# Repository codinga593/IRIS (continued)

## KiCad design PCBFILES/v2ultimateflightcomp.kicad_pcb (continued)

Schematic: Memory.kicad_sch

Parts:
C1: 10uF; C_0402_1005Metric
IC1: W25Q128JVFIQ; SOIC127P1032X264-16N; Mouser Part Number 454-W25Q128JVFIQ
R11: 10k; R_0402_1005Metric

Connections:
+3V3: C1.2, IC1.1 (IO3), IC1.2 (VCC), IC1.9 (IO2), R11.1; also elsewhere on the board
CS_FLASH: IC1.7 (~CS), R11.2; also elsewhere on the board
GND: C1.1, IC1.10 (GND); also elsewhere on the board
MISO_FLASH: IC1.8 (DO_(IO1)); also elsewhere on the board
MOSI_FLASH: IC1.15 (DI_(IO0)); also elsewhere on the board
SCK_FLASH: IC1.16 (CLK); also elsewhere on the board

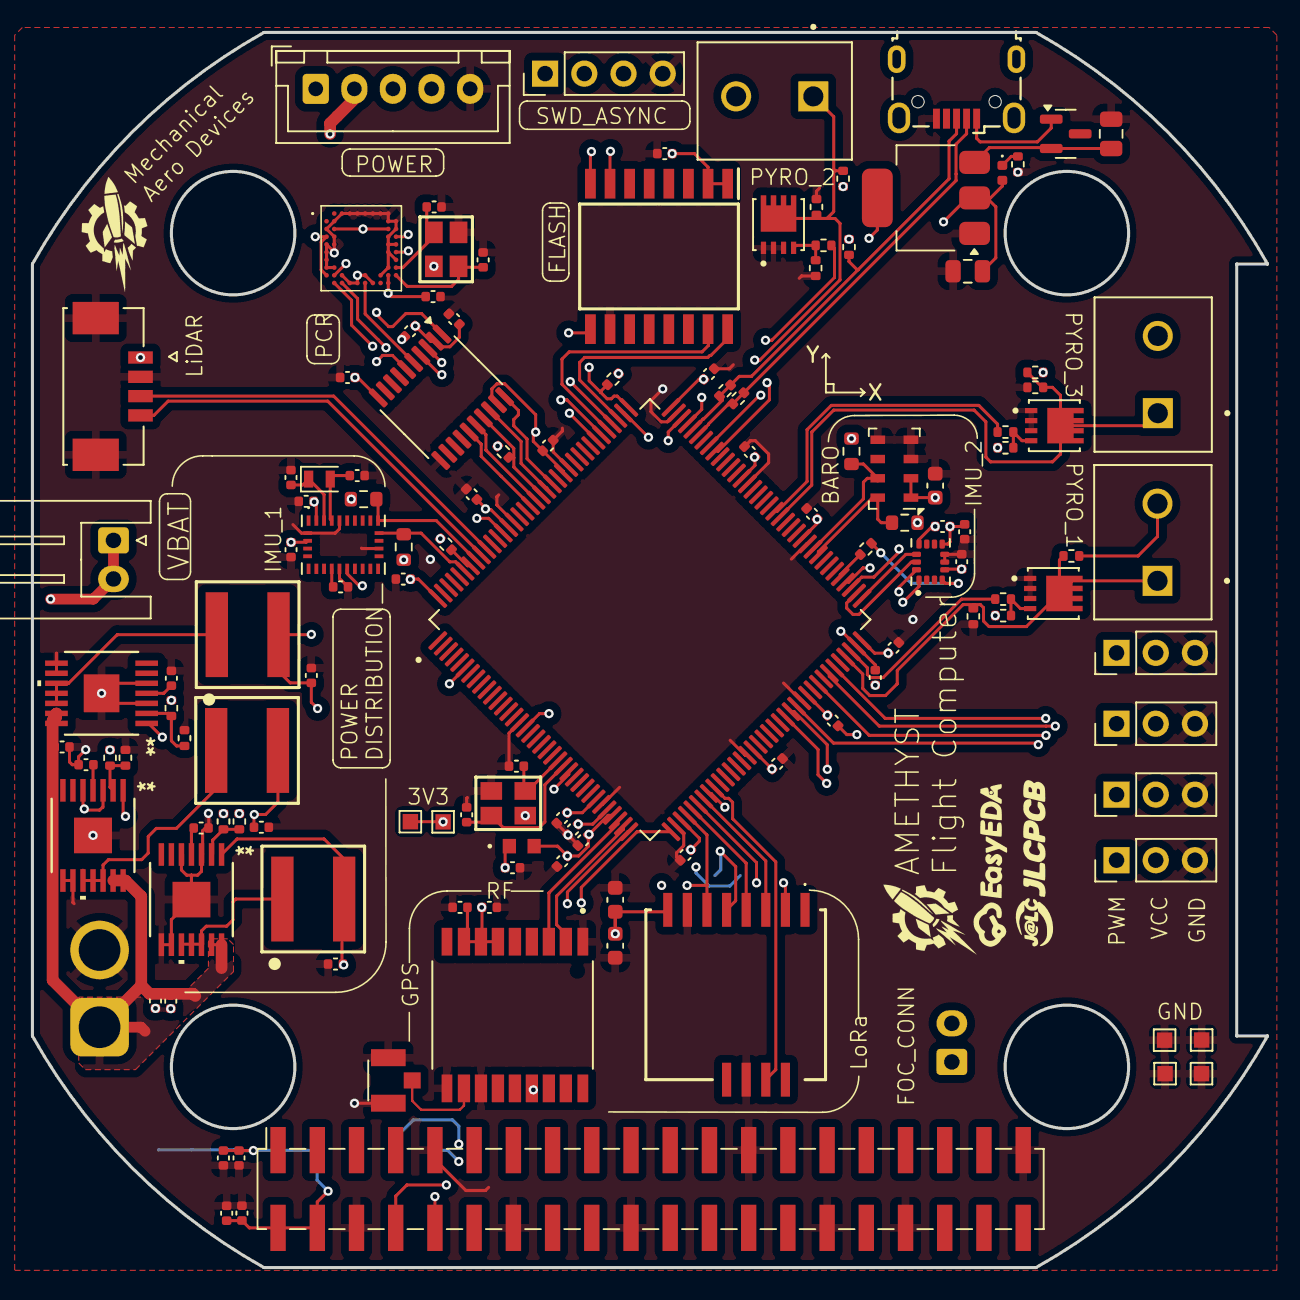
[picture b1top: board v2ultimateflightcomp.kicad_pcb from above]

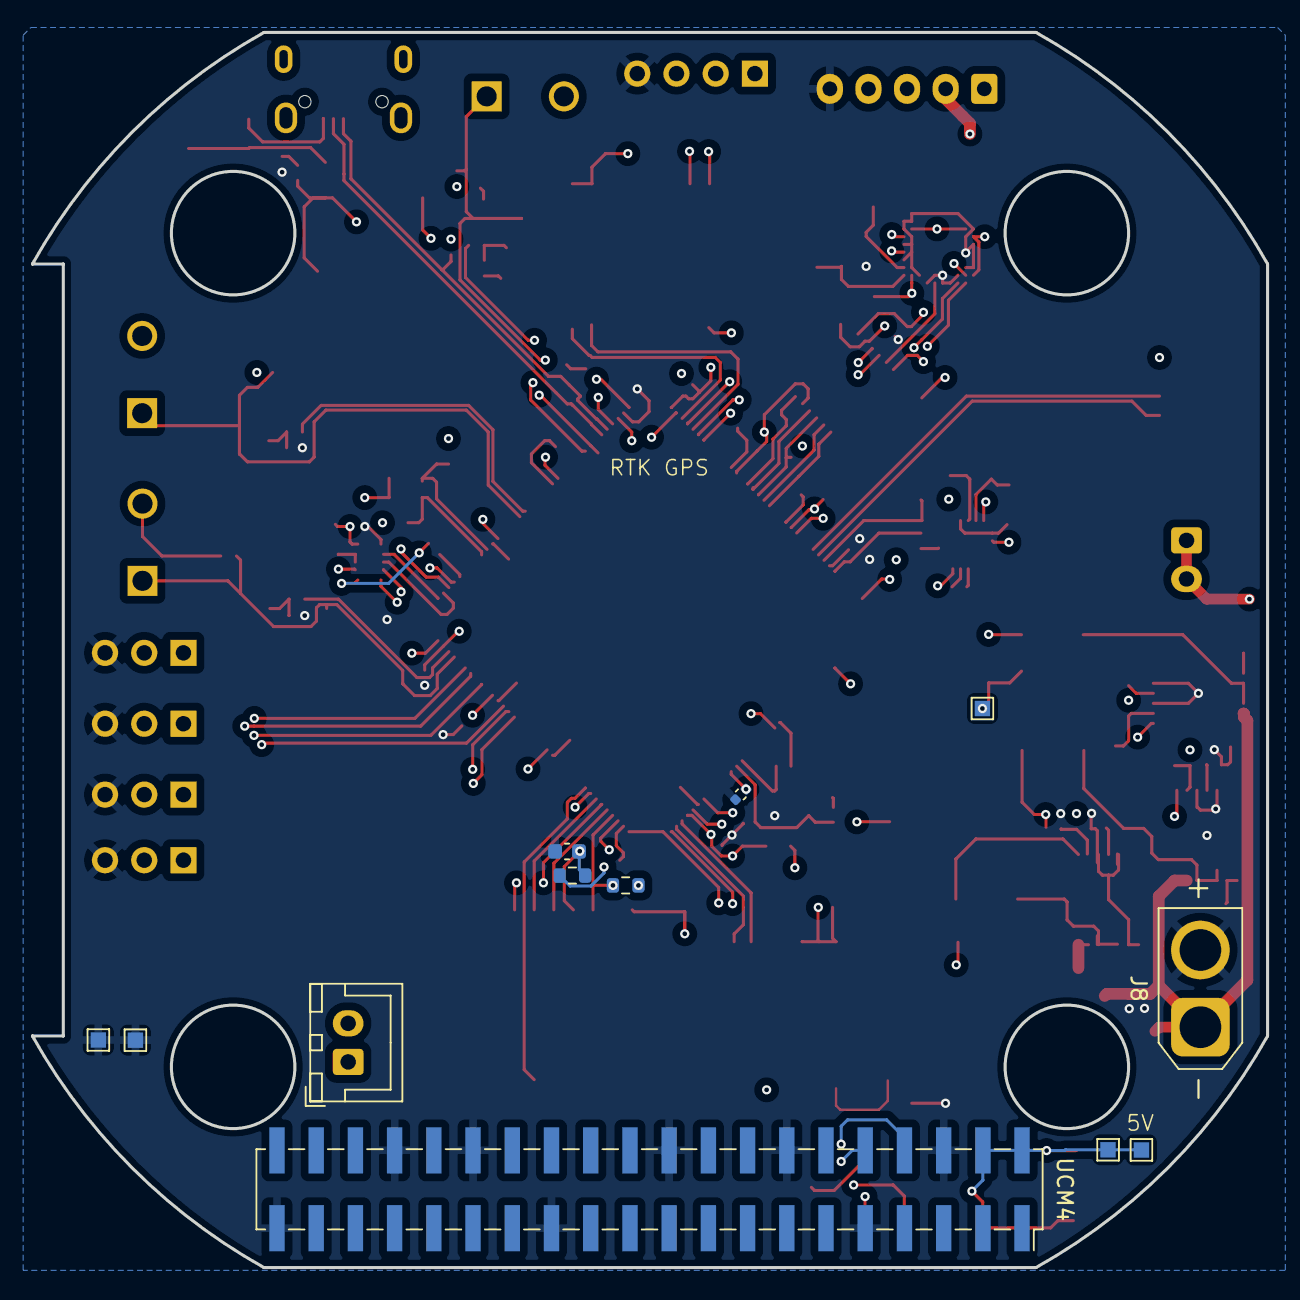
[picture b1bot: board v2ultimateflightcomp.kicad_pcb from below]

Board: 6 copper layers, 80.0 x 80.0 mm, 140 parts (12 on the bottom side), 86 nets.

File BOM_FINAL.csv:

Designator,Part Name,Qty,Value / Part Number,Link
"C66,C95,C26,C49,C28,C67,C55,C29,C33,C22,C48,C54,C19,C34,C30,C58,C41,C42,C20,C45,C46,C39,C18,C93,C47,C32,C21,C25,C27,C88,C35",Ceramic Capacitor,31,"100nF, 0402, Samsung CL05B104KO5NNNC (JLC C1525)",https://jlcpcb.com/partdetail/1877-CL05B104KO5NNNC/C1525
"C23,C24,C61,C60",Ceramic Capacitor,4,"24pF, 0402, C0G/NP0, FH 0402CG240J500NT (LCSC C1553)",https://www.lcsc.com/product-detail/C1553.html
U3,IMU,1,BNO085 (JLC C5189642),https://jlcpcb.com/partdetail/CEVA-BNO085/C5189642
"J9,J1,J10,J11",Socket Header,4,"1x03, 2.54mm, vertical, Amphenol SIP050-1X03-157BLF",https://www.digikey.com/en/products/detail/amphenol-cs-fci/S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
"R45,R48,R46,R47,R49,R44",Resistor,6,TBD - source BOM only says 'R' (exact value not specified),
"R21,R14,R22,R17",Resistor,4,"4.7kΩ, 0603, UNI-ROYAL 0603WAF4701T5E (LCSC C23162)",https://www.lcsc.com/product-detail/C23162.html
"TP13,TP9,TP14,TP6,TP11,TP10,TP16,TP15,TP5,TP8,TP7",Test Point,11,PCB test pad 1.0x1.0mm - no discrete purchasable part specified,
"URpiZero1,UCM4",Socket Header,2,"2x20 Raspberry Pi socket/riser header, Adafruit 4079",https://www.digikey.com.au/en/products/detail/adafruit-indus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
"R10,R18,R28",Resistor,3,"100kΩ, 0402, UNI-ROYAL 0402WGF1003TCE (JLC/LCSC C25741)",https://www.lcsc.com/product-detail/C25741.html
"Q2,Q4,Q3",MOSFET,3,"BSZ100N06LS3 G, Infineon",https://www.digikey.com/en/products/detail/infineon-technolo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
"C53,C92,C90,C94",Ceramic Capacitor,4,"10uF, 0402, Samsung CL05A106MQ5NUNC (JLC C15525)",https://jlcpcb.com/partdetail/16204-CL05A106MQ5NUNC/C15525
"R6,R32,R8,R1",Resistor,4,"100Ω, 0402, Ever Ohms CR0402F100RQ10 (JLC C429511)",https://jlcpcb.com/partdetail/Ever_OhmsTech-CR0402F100RQ10/C429511
J14,Pin Header,1,"1x04, 2.54mm, vertical, generic 4-pin header",https://newhavendisplay.com/1x4-single-row-pin-header-connector/
J17,RF Connector,1,Hirose U.FL-R-SMT(01),https://www.digikey.com.au/en/products/detail/hirose-electri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
U5,Barometer,1,MS5611-01BA03 / MS561101BA03-50 (JLC C15639),https://jlcpcb.com/partdetail/TEConnectivity-MS561101BA0350/C15639
C37,Ceramic Capacitor,1,"10uF, 0603, Samsung CL10A106MA8NRNC (LCSC C96446)",https://www.lcsc.com/product-detail/C96446.html
"C91,C86,C89",Ceramic Capacitor,3,"22uF, 0402, JLCPCB Assembly 22uF/16V (JLC C9900105298)",https://jlcpcb.com/partdetail/JLCPCBAssembly-22uF16V/C9900105298
"C84,C85",Ceramic Capacitor,2,"10pF, 0402, FH 0402CG100J500NT (JLC C1545)",https://jlcpcb.com/partdetail/1897-0402CG100J500NT/C1545
"L11,L10,L9",Inductor,3,"6.8uH, Würth WE-XHMA 6060",https://www.mouser.com/ProductDetail/Wurth-Elektronik/74437368068
"R34,R33",Resistor,2,"22Ω, 0402, YAGEO RC0402FR-0722RL (LCSC C114765)",https://www.lcsc.com/product-detail/C114765.html
"J5,J3,J4",Terminal Block,3,Same Sky / CUI TB002-500-02BE,https://www.digikey.com.au/en/products/detail/same-sky-forme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
"Y1,Y3",Crystal,2,"24MHz, 3225, Suzhou Liming 3225-24.00-20-10-10/A (JLC C518165)",https://jlcpcb.com/partdetail/534702-3225_24_00_20_10_10A/C518165
C31,Ceramic Capacitor,1,"10uF, 0402, Samsung CL05A106MQ5NUNC (JLC C15525)",https://jlcpcb.com/partdetail/16204-CL05A106MQ5NUNC/C15525
J6,JST Header,1,"JST B5B-XH-A, 5-pin, 2.50mm, vertical",https://www.digikey.com/en/products/detail/jst-sales-america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
IC2,LoRa Module,1,Seeed 114993390 / Wio-SX1262,https://www.digikey.com/en/products/detail/seeed-technology-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
U2,LDO Regulator,1,"AMS1117-3.3, SOT-223 (JLC C6186)",https://jlcpcb.com/partdetail/Advanced_MonolithicSystems-AMS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
U4,IMU,1,ICM-42688-P (JLC C1850418),https://jlcpcb.com/partdetail/TDKInvenSense-ICM_42688P/C1850418
"U11,U12,U13",Buck Converter,3,TPS54525PWPR (JLC C140350),https://jlcpcb.com/partdetail/TexasInstruments-TPS54525PWPR/C140350
"C36,C38,C56",Ceramic Capacitor,3,"100nF, 0603, YAGEO CC0603KRX7R9BB104 (LCSC C14663)",https://www.lcsc.com/product-detail/C14663.html
IC1,NOR Flash,1,W25Q128JVFIQ (JLC C111478),https://jlcpcb.com/partdetail/WinbondElec-W25Q128JVFIQ/C111478
"R15,R2,R7,R9,R11,R5,R29,R12,R27",Resistor,9,"10kΩ, 0402, UNI-ROYAL 0402WGF1002TCE (JLC C25744)",https://jlcpcb.com/partdetail/26487-0402WGF1002TCE/C25744
"R3,R4",Resistor,2,"1.5kΩ, 0402, UNI-ROYAL 0402WGF1501TCE (LCSC C25867)",https://www.lcsc.com/product-detail/C25867.html
U1,MCU,1,STM32H753ZIT6 (JLC C730207),https://jlcpcb.com/partdetail/STMicroelectronics-STM32H753ZI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
"C3,C2",Ceramic Capacitor,2,"22uF, 0805, Samsung CL21A226MAYNNNE (LCSC C45783)",https://www.lcsc.com/product-detail/C45783.html
C59,Ceramic Capacitor,1,"10nF, 0402, Kyocera AVX 0402YC103K4T2A (JLC C2172121)",https://jlcpcb.com/partdetail/KyoceraAVX-0402YC103K4T2A/C2172121
Y4,Crystal,1,TBD - source BOM says only 'Crystal' in 2012 package,
IC7,Radar Sensor,1,Acconeer A121-001-T&R / A121,https://www.mouser.com/ProductDetail/Acconeer/A121-001-TR
D2,LED,1,TBD - source BOM says only 'LED' in 0402 package,
C1,Ceramic Capacitor,1,"10uF, 0402, Samsung CL05A106MQ5NUNC (JLC C15525)",https://jlcpcb.com/partdetail/16204-CL05A106MQ5NUNC/C15525
J7,Molex PicoBlade Header,1,Molex 53261-0471,https://www.digikey.com/en/products/detail/molex/0532610471/699096
"C40,C17",Ceramic Capacitor,2,"2.2uF, 0402, Samsung CL05A225MQ5NSNC (JLC C12530)",https://jlcpcb.com/partdetail/13164-CL05A225MQ5NSNC/C12530
J18,USB Connector,1,"Würth 629105150521, Micro USB B",https://www.digikey.com.au/en/products/detail/w%C3%BCrth-ele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
U7,Level Shifter,1,TXS0108EPWR (JLC C17206),https://jlcpcb.com/partdetail/TexasInstruments-TXS0108EPWR/C17206
FB1,Ferrite Bead,1,Sunlord GZ1608D601TF (JLC C1002),https://jlcpcb.com/partdetail/Sunlord-GZ1608D601TF/C1002
D3,Schottky Diode,1,"BAT54A, SOT-23 (JLC C397609)",https://jlcpcb.com/partdetail/AnBon-BAT54A/C397609
J12,JST Header,1,"JST S2B-XH-A, 2-pin, 2.50mm, right-angle",https://www.digikey.com/en/products/detail/jst-sales-america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
U10,GNSS Module,1,u-blox MAX-M10S-00B (JLC C4153167),https://jlcpcb.com/partdetail/UBLOX-MAX_M10S00B/C4153167
J8,XT30 Connector,1,AMASS XT30U-M (JLC C99101),https://jlcpcb.com/partdetail/Changzhou_AmassElec-XT30UM/C99101
"R20,R19",Resistor,2,"10kΩ, 0603, YAGEO RC0603FR-0710KL (LCSC C98220)",https://www.lcsc.com/product-detail/C98220.html
J2,JST Header,1,"JST B2B-XH-A, 2-pin, 2.50mm, vertical",https://www.digikey.com/en/products/detail/jst-sales-america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

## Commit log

2026-04-05 Create file creator
2026-04-05 Create filecreator
2026-04-05 Add Existing File
